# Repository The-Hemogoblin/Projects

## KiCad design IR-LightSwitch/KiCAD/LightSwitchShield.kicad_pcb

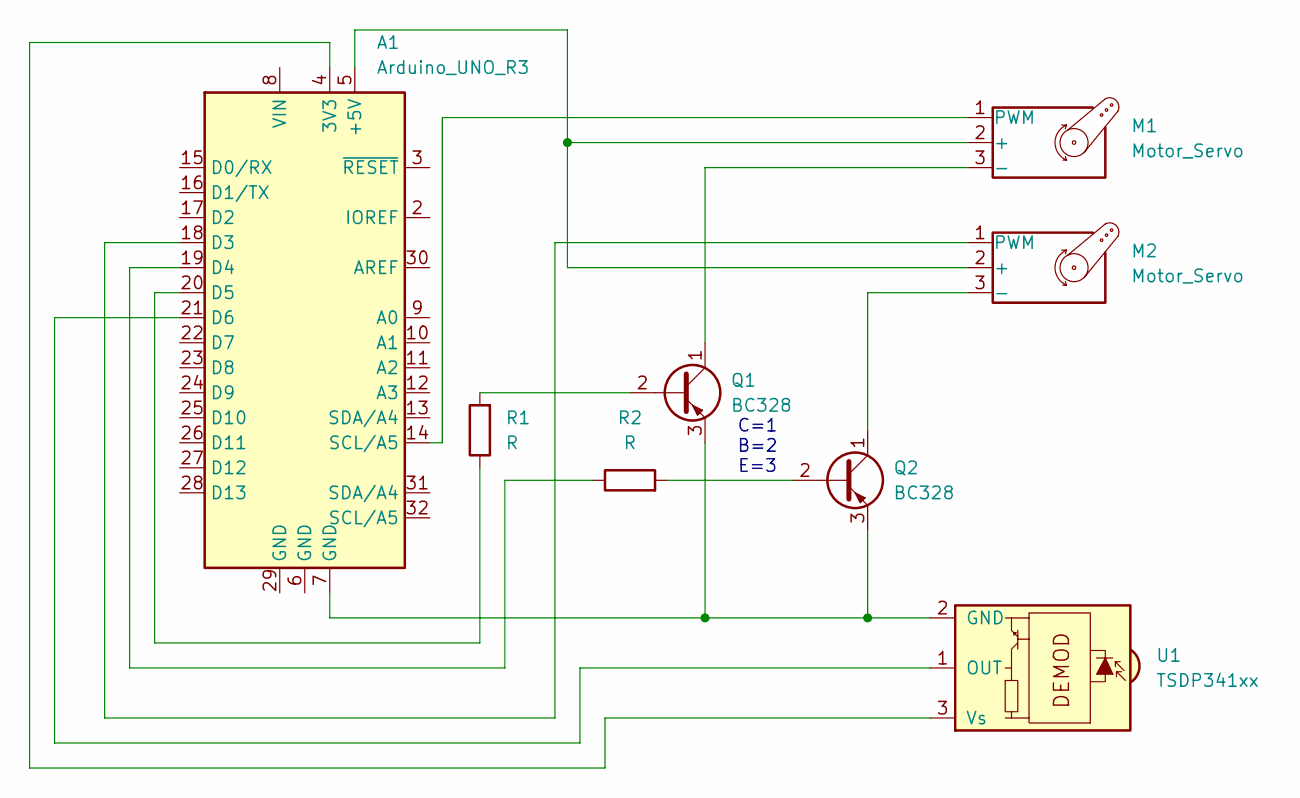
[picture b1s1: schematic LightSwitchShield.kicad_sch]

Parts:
A1: Arduino_UNO_R3
M1, M2: Motor_Servo; PinHeader_1x03_P2.54mm_Vertical
Q1, Q2: BC328; TO-92_Inline
R1, R2: R; R_Axial_DIN0204_L3.6mm_D1.6mm_P2.54mm_Vertical
U1: TSDP341xx; PinHeader_1x03_P2.54mm_Vertical

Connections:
unnamed: A1.4 (3V3), U1.3 (Vs)
unnamed: A1.5 (+5V), M1.2 (+), M2.2 (+)
unnamed: A1.18 (D3), M2.1 (PWM)
unnamed: A1.19 (D4), R2.1
unnamed: A1.20 (D5), R1.1
unnamed: A1.21 (D6), U1.1 (OUT)
unnamed: M1.3 (-), Q1.1 (C)
unnamed: A1.14 (SCL/A5), M1.1 (PWM)
unnamed: M2.3 (-), Q2.1 (C)
unnamed: Q1.2 (B), R1.2
unnamed: A1.7 (GND), Q1.3 (E), Q2.3 (E), U1.2 (GND)
unnamed: Q2.2 (B), R2.2

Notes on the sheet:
C=1 B=2 E=3

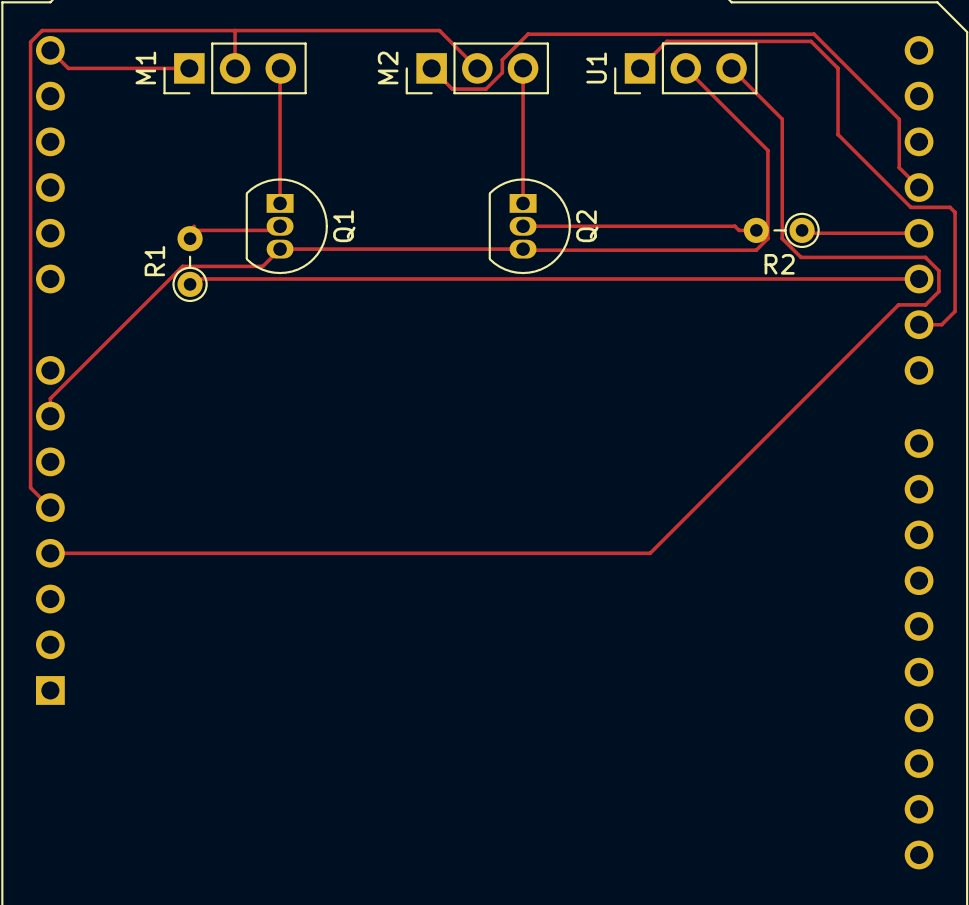
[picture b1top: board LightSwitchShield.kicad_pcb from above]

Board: 2 copper layers, 8 parts (0 on the bottom side), 12 nets.

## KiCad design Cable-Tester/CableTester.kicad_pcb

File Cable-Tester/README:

A single PCB ran with a 3v coin battery whose goal is to be able to test if cables run only power, data, or both

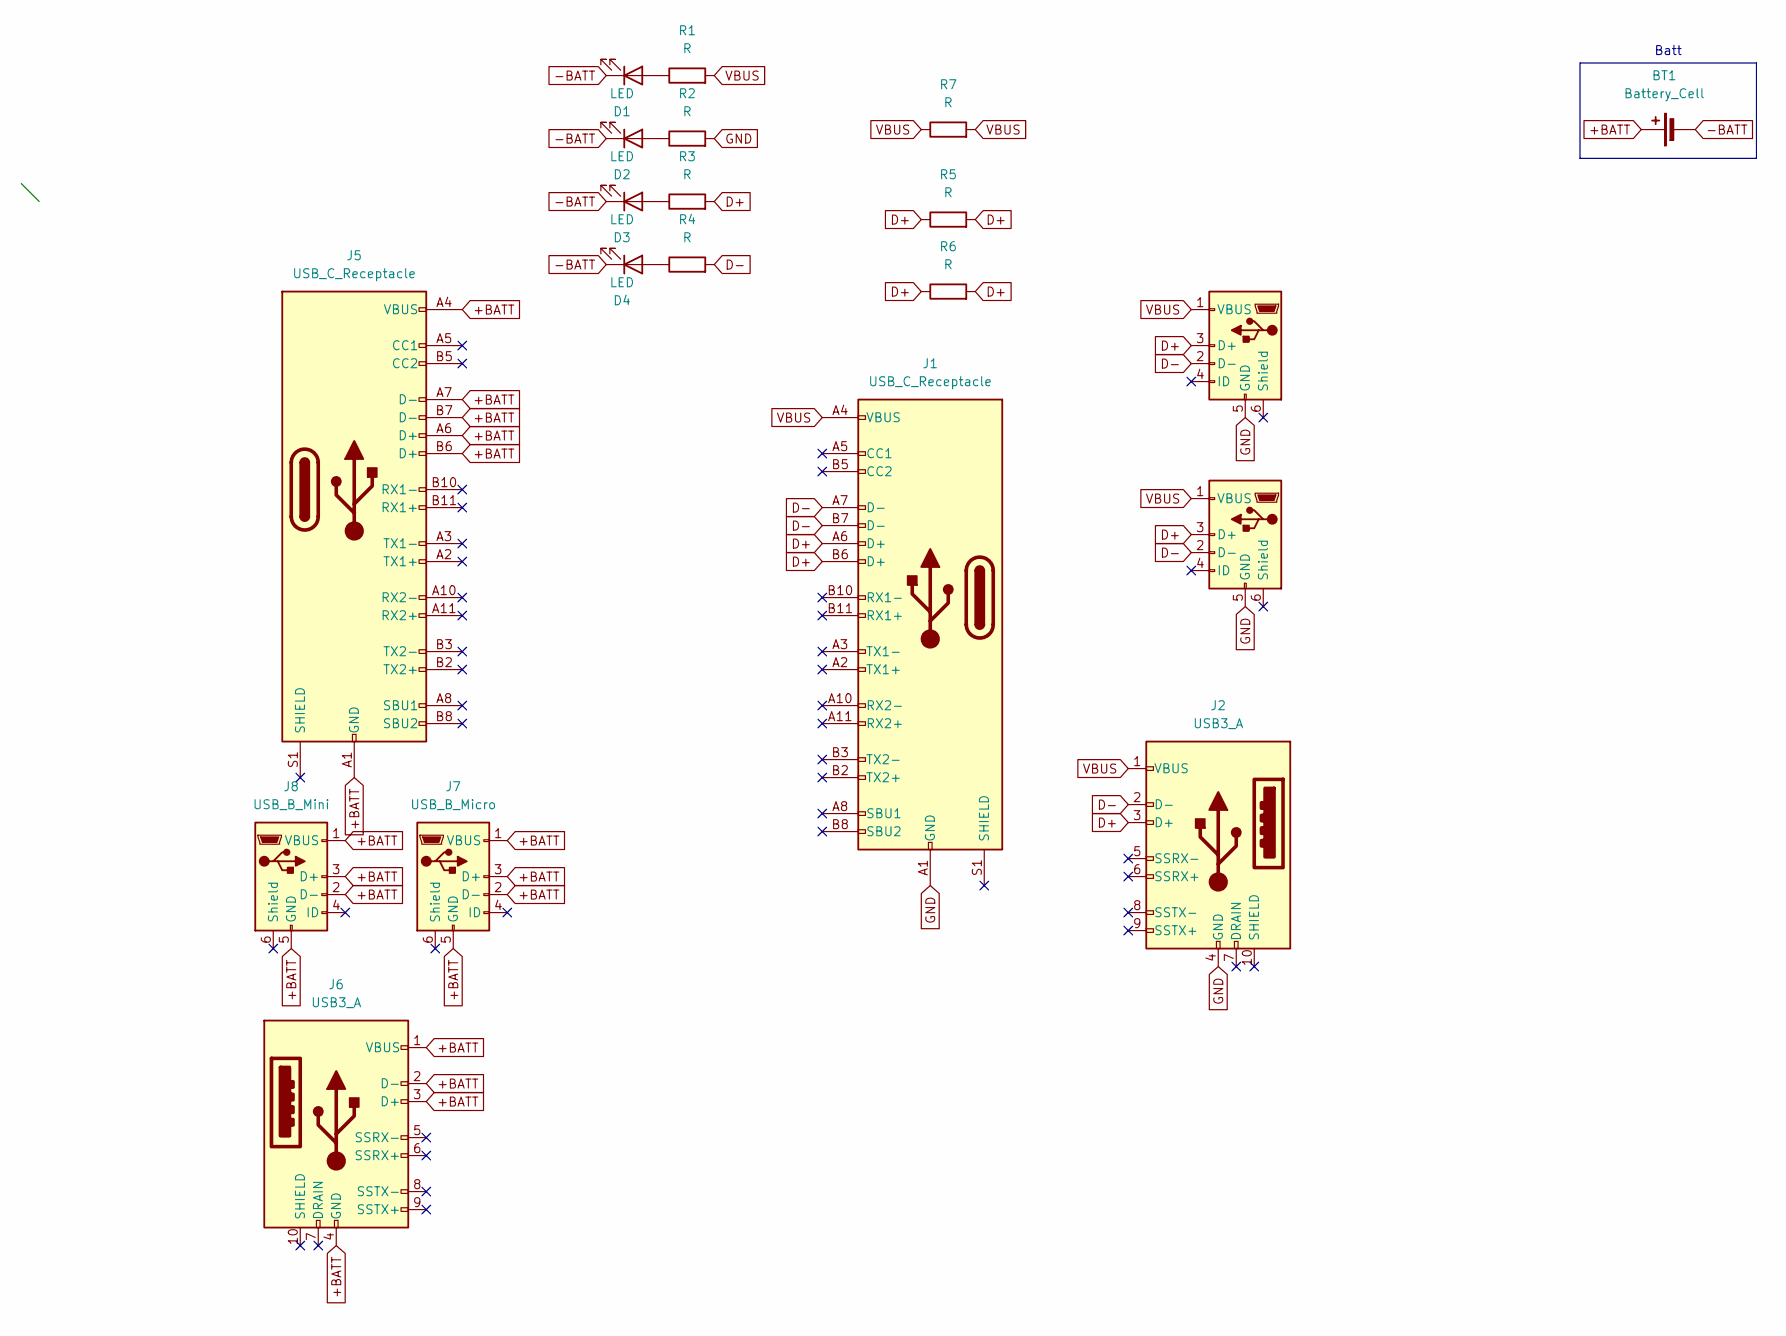
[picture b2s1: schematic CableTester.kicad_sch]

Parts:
BT1: Battery_Cell; BatteryHolder_MYOUNG_BS-07-A1BJ001_CR2032
D1, D2, D3, D4: LED; LED_0201_0603Metric_Pad0.64x0.40mm_HandSolder
J1, J5: USB_C_Receptacle; USB_C_Receptacle_Amphenol_12401610E4-2A
J2, J6: USB3_A; USB3_A_Molex_48393-001
J3, J7: USB_B_Micro; USB_Micro-AB_Molex_47590-0001
J4, J8: USB_B_Mini; USB_Mini-B_Lumberg_2486_01_Horizontal
R1, R2, R3, R4: R; R_0201_0603Metric_Pad0.64x0.40mm_HandSolder
R5, R6, R7: R; R_2010_5025Metric

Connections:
+BATT: BT1.1 (+), J5.A1 (GND), J5.A4 (VBUS), J5.A6 (D+), J5.A7 (D-), J5.A9 (VBUS), J5.A12 (GND), J5.B1 (GND), J5.B4 (VBUS), J5.B6 (D+), J5.B7 (D-), J5.B9 (VBUS), J5.B12 (GND), J6.1 (VBUS), J6.2 (D-), J6.3 (D+), J6.4 (GND), J7.1 (VBUS), J7.2 (D-), J7.3 (D+), J7.5 (GND), J8.1 (VBUS), J8.2 (D-), J8.3 (D+), J8.5 (GND)
-BATT: BT1.2 (-), D1.1 (K), D2.1 (K), D3.1 (K), D4.1 (K)
D+: J1.A6 (D+), J1.B6 (D+), J2.3 (D+), J3.3 (D+), J4.3 (D+), R3.2, R5.1, R5.2, R6.1, R6.2
D-: J1.A7 (D-), J1.B7 (D-), J2.2 (D-), J3.2 (D-), J4.2 (D-), R4.2
GND: J1.A1 (GND), J1.A12 (GND), J1.B1 (GND), J1.B12 (GND), J2.4 (GND), J3.5 (GND), J4.5 (GND), R2.2
unnamed: D1.2 (A), R1.1
unnamed: D2.2 (A), R2.1
unnamed: D3.2 (A), R3.1
unnamed: D4.2 (A), R4.1
VBUS: J1.A4 (VBUS), J1.A9 (VBUS), J1.B4 (VBUS), J1.B9 (VBUS), J2.1 (VBUS), J3.1 (VBUS), J4.1 (VBUS), R1.2, R7.1, R7.2

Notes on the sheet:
Batt

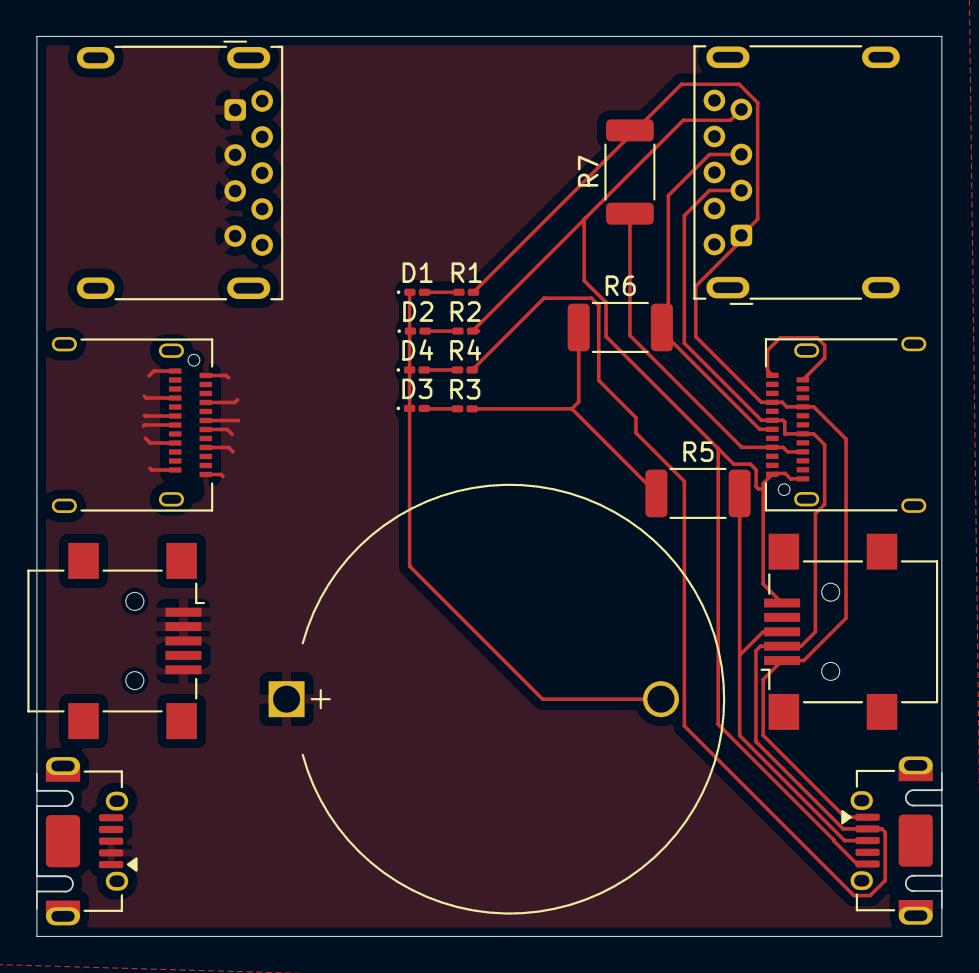
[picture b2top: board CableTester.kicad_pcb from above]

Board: 2 copper layers, 50.3 x 50.0 mm, 20 parts (0 on the bottom side), 10 nets.

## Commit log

2026-02-26 Create placeholder
2026-02-26 Rename LucasRCLightSwitchxFan.ino to LucasRCLightSwitchxFan.ino
2026-02-26 Rename Watch/SeeedStudioWatch.kicad_pcb to Watch/KiCAD/SeeedStudioWatch.kicad_pcb
2026-02-26 Rename Watch/SeeedStudioWatch.kicad_prl to Watch/KiCAD/SeeedStudioWatch.kicad_prl
2026-02-26 Rename Watch/SeeedStudioWatch.kicad_pro to Watch/KiCAD/SeeedStudioWatch.kicad_pro
2026-02-26 Rename Watch/SeeedStudioWatch.kicad_sch to Watch/KiCAD/SeeedStudioWatch.kicad_sch
2026-02-26 Rename Watch/fp-info-cache to Watch/KiCAD/fp-info-cache
2026-02-26 Rename IR-LightSwitch/LucasRCLightSwitchxFan.ino to IR-LightSwitch/Code/RCLightSwitchxFan.ino
2026-02-26 Rename Filament-Dryer/fp-info-cache to Filament-Dryer/KiCAD/fp-info-cache
2026-02-26 Rename Filament-Dryer/ThermisistorTest.kicad_pcb to Filament-Dryer/KiCAD/ThermisistorTest.kicad_pcb
2026-02-26 Rename Filament-Dryer/ThermisistorTest.kicad_sch to Filament-Dryer/KiCAD/ThermisistorTest.kicad_sch
2026-02-26 Rename Filament-Dryer/ThermisistorTest.kicad_prl to Filament-Dryer/KiCAD/ThermisistorTest.kicad_prl
2026-02-26 Rename Filament-Dryer/ThermisistorTest.kicad_pro to Filament-Dryer/KiCAD/ThermisistorTest.kicad_pro
2026-04-22 Update OLED_Clock.ino
    Fixed needing serial to start and added month listing
2026-04-22 Update OLED_Clock.ino
    forgot legit one thing that shouldnt be commented smh my head
